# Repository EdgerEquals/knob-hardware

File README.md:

# knob-hardware

This repo holds the hardware for Ed's motorised knob and its Eurorack module (10HP).

- `cad/` is the parametric parts library. Each part folder has a build123d script, STEP, DXF and drawing PNG. The parts index is in `cad/README.md`.
- PCBs live in KiCad projects under `cad/pcbs/`, which are the single source of truth. Board STEPs are exported from KiCad and feed the mechanical assemblies.
- Dimensions marked [A] are assumed and need checking with calipers.
- `cad/knob-param/` (branch `param-dev`) is the sub-assembly-split parametric model of the whole knob stack, set up for parallel cloud-agent work. Start with `cad/knob-param/AGENTS.md`.

## Docs

- [Design notes](docs/design-notes.md): the current knob-module design (CAD v0.16), check status and open items.
- [Top screen joystick](docs/top-screen-joystick.md): the sliding screen carrier on the Alps SKRHADE010 and the switch shortlist.
- [Manufacturing (PCBWay)](docs/manufacturing-pcbway.md): the kit plan, what PCBWay builds, the cost target and reviewer questions.

The software engine lives in EdgerEquals/dad-page.

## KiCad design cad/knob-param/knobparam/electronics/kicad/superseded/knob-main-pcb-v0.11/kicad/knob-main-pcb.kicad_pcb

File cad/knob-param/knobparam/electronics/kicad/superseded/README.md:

# Superseded boards and tools (archived 10 Nov 2026)

Kept for the record only. **Nothing here is current, nothing here should be quoted or ordered**, and the scripts are not
run by the model (their relative paths broke when they moved here). See `docs/leftover-sweep-2026-11-10.md`.

| Folder | What it was | Replaced by |
|---|---|---|
| `knob-main-pcb-v0.11/` | main board v0.11 (generator, KiCad files, fab pack, STEP, DXF, drawing) | `../knob-main-pcb/v2/` (6 layers, routed, fab pack v2.0) |
| `screen-adapter-v0.4/` | screen adapter v0.4 (Ø15.5, CH32V003, FPC14) | the Ø12 rod-link board (v0.24) |
| `joystick-daughterboard-v0.4/` | joystick daughterboard v0.1/v0.4 (four M2 standoffs, 1x3 long headers) | the joystick top board on the vertical boards (layout v4); its `geom.json` stays in `../joystick-daughterboard/` because the model reads it |
| `v016-pipeline/` | the v0.16b board pipeline: `export_cad_constraints.py` → `cad_constraints.json` → `make_v016_footprints.py`, the old `export_pcb_proxy.py` (it wrote the same `pcb_proxy.json` the model reads, from the v0.11 board), `joystick_stack_v016.json` | `../knob-main-pcb/v2/design.py`, `make_board.py`, `export_proxy.py` |

`cad/pcbs/` (outside the model) is the separate v0.11 snapshot kept for `main`, untouched.

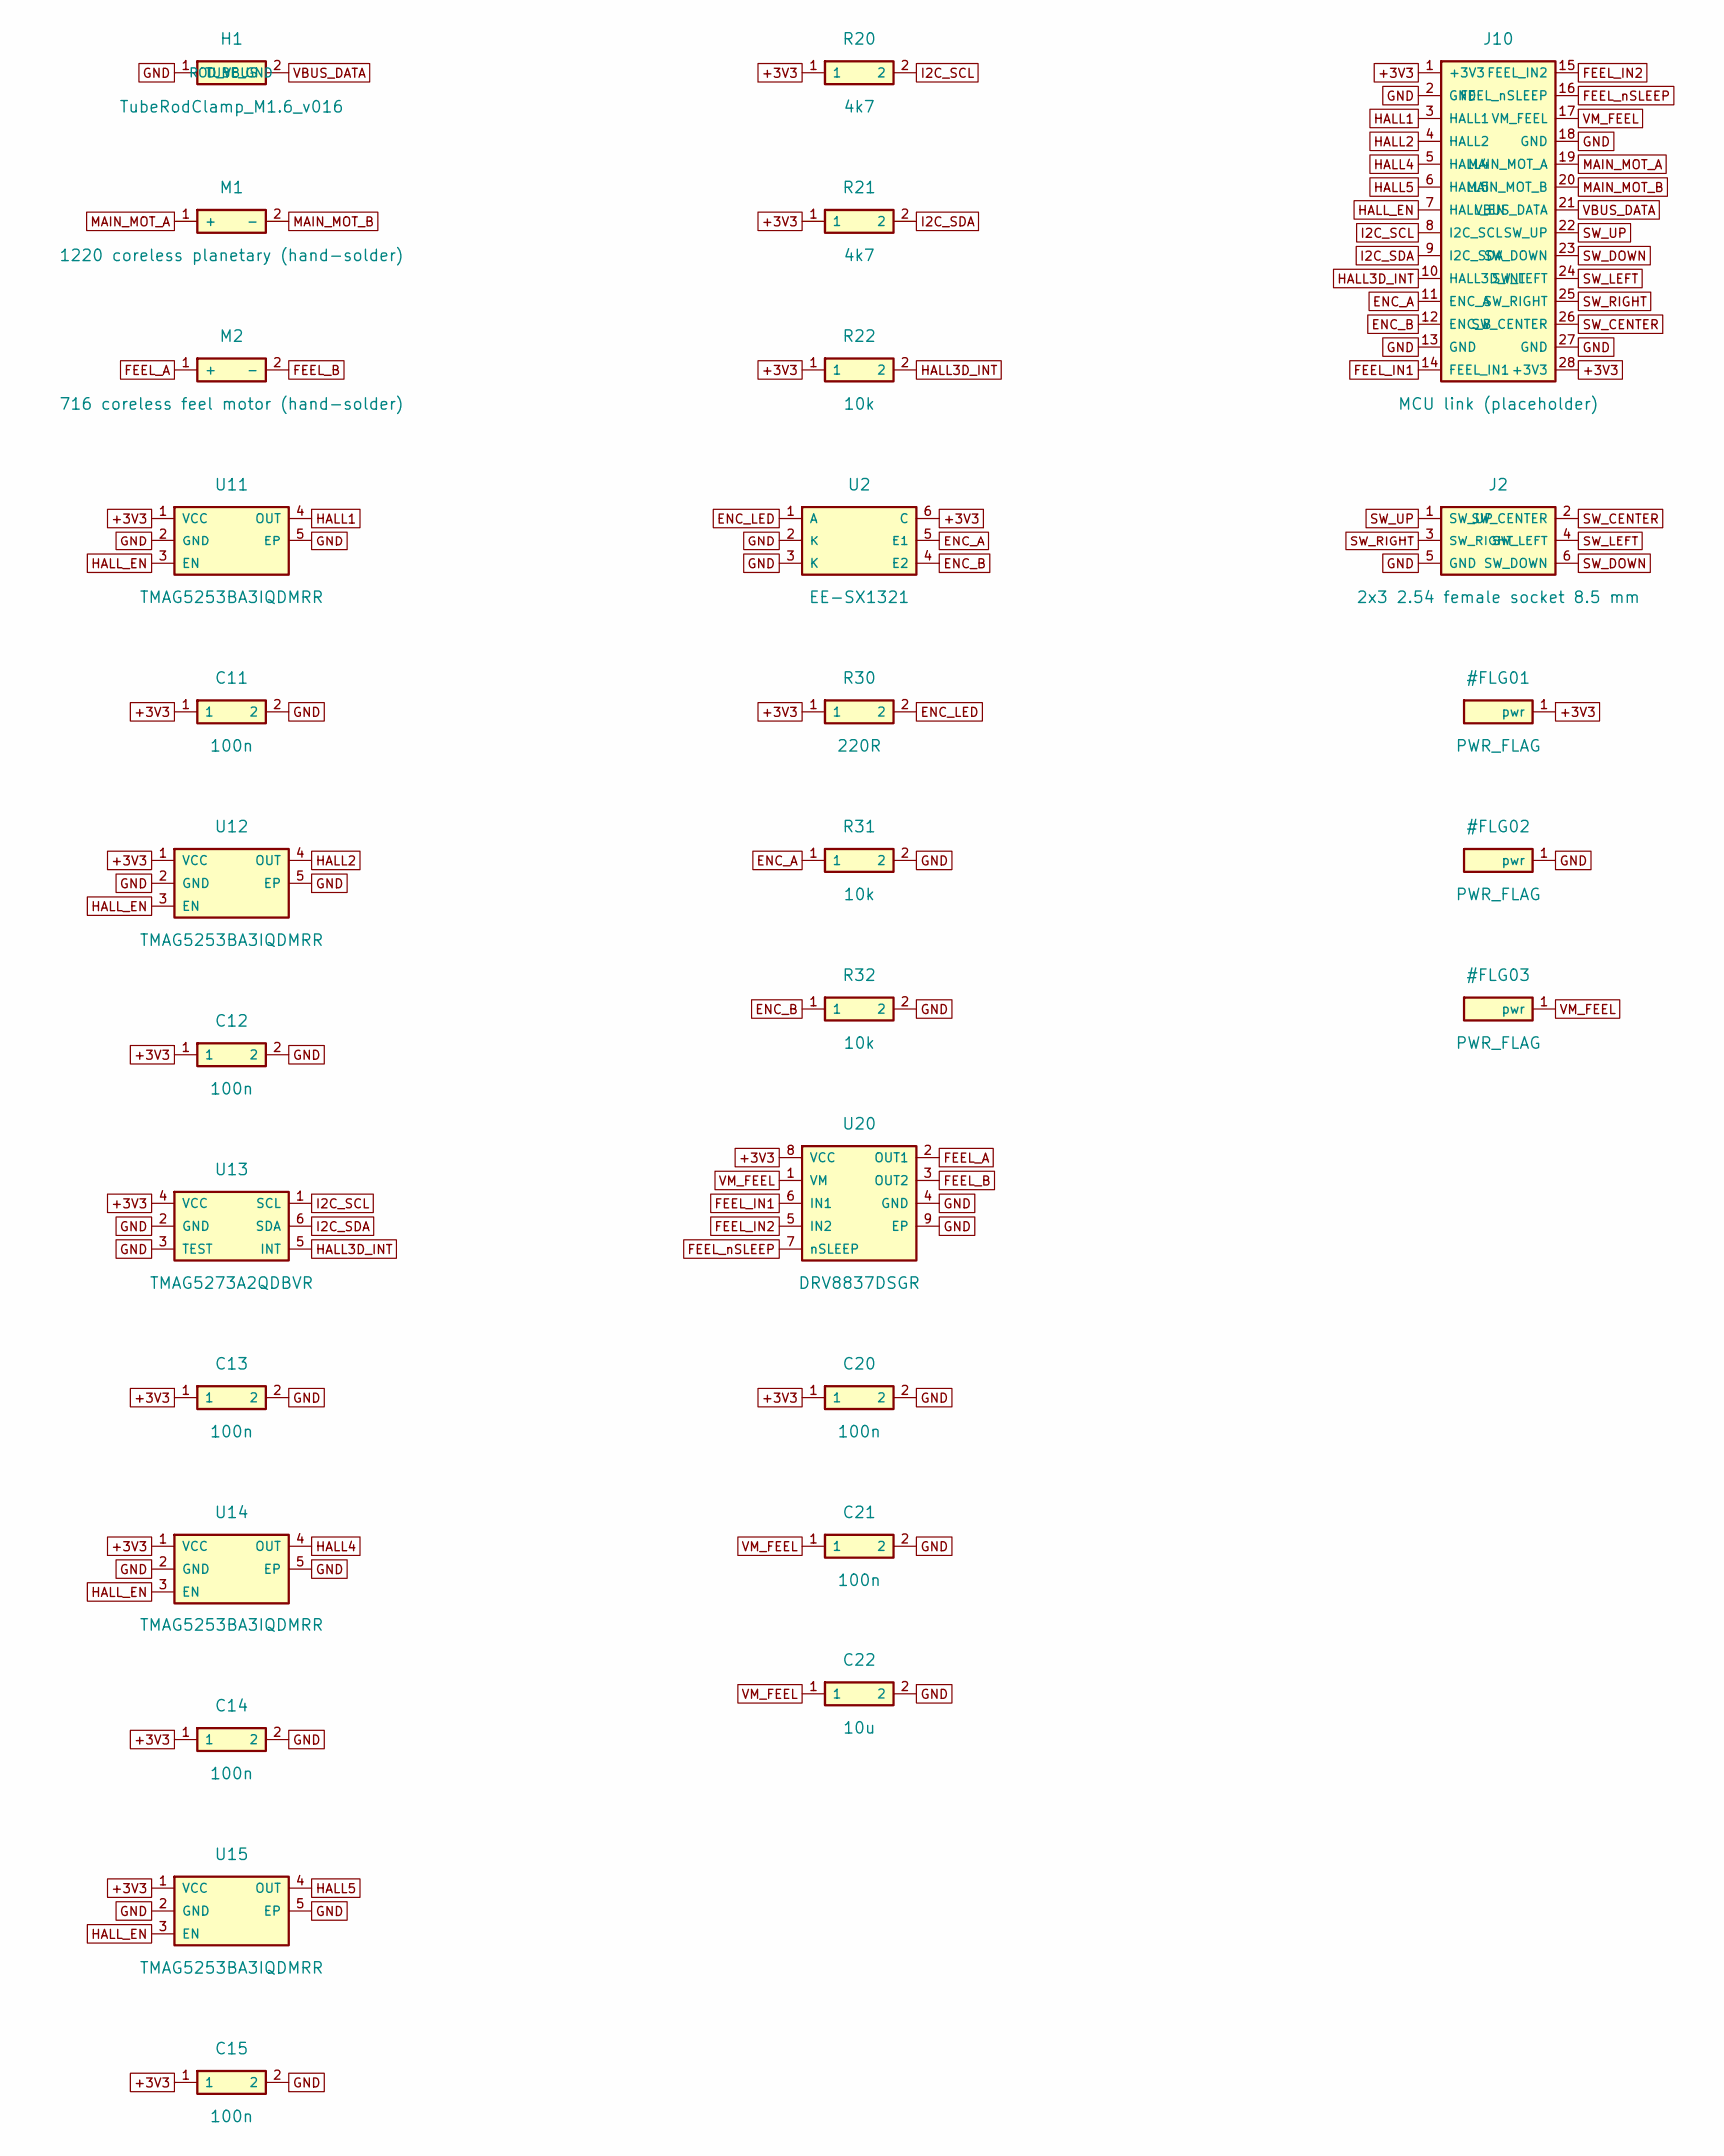
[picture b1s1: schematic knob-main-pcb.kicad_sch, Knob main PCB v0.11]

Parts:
C11, C12, C13, C14, C15, C20, C21: 100n; C_0402; MPN CL05B104KO5NNNC; LCSC C1525
C22: 10u; C_0603; MPN CL10A106KP8NNNC; LCSC C19702
H1: TubeRodClamp_M1.6_v016; TubeRodClamp_Main_M1.6_v016
J2: 2x3 2.54 female socket 8.5 mm; PinSocket_2x03_P2.54_Vertical_8.5mm; MPN FG-PM2.54-2-03P-H8.5; LCSC C42391433
J10: MCU link (placeholder); Pads_2x14_P2.00_SMD
M1: 1220 coreless planetary (hand-solder); Motor_1220_Tabs_Relief
M2: 716 coreless feel motor (hand-solder); FeelMotor_716_LeadPads
R20, R21: 4k7; R_0402; MPN 0402WGF4701TCE; LCSC C25900
R22, R31, R32: 10k; R_0402; MPN RC0402FR-0710KL; LCSC C60490
R30: 220R; R_0402; MPN 0402WGF2200TCE; LCSC C25091
U2: EE-SX1321; Omron_EE-SX1321; MPN EE-SX1321; LCSC C469128
U11, U12, U14, U15: TMAG5253BA3IQDMRR; X2SON-4_TMAG5253; MPN TMAG5253BA3IQDMRR; LCSC C22401868
U13: TMAG5273A2QDBVR; SOT-23-6_TMAG5273_Tight; MPN TMAG5273A2QDBVR; LCSC C3715882
U20: DRV8837DSGR; WSON-8_2x2_DRV8837; MPN DRV8837DSGR; LCSC C39159

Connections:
+3V3: C11.1, C12.1, C13.1, C14.1, C15.1, C20.1, J10.1 (+3V3), J10.28 (+3V3), R20.1, R21.1, R22.1, R30.1, U2.6 (C), U11.1 (VCC), U12.1 (VCC), U13.4 (VCC), U14.1 (VCC), U15.1 (VCC), U20.8 (VCC)
ENC_A: J10.11 (ENC_A), R31.1, U2.5 (E1)
ENC_B: J10.12 (ENC_B), R32.1, U2.4 (E2)
ENC_LED: R30.2, U2.1 (A)
FEEL_A: M2.1 (+), U20.2 (OUT1)
FEEL_B: M2.2 (-), U20.3 (OUT2)
FEEL_IN1: J10.14 (FEEL_IN1), U20.6 (IN1)
FEEL_IN2: J10.15 (FEEL_IN2), U20.5 (IN2)
FEEL_nSLEEP: J10.16 (FEEL_nSLEEP), U20.7 (nSLEEP)
GND: C11.2, C12.2, C13.2, C14.2, C15.2, C20.2, C21.2, C22.2, H1.1 (TUBE_GND), J2.5 (GND), J10.2 (GND), J10.13 (GND), J10.18 (GND), J10.27 (GND), R31.2, R32.2, U2.2 (K), U2.3 (K), U11.2 (GND), U11.5 (EP), U12.2 (GND), U12.5 (EP), U13.2 (GND), U13.3 (TEST), U14.2 (GND), U14.5 (EP), U15.2 (GND), U15.5 (EP), U20.4 (GND), U20.9 (EP)
HALL1: J10.3 (HALL1), U11.4 (OUT)
HALL2: J10.4 (HALL2), U12.4 (OUT)
HALL3D_INT: J10.10 (HALL3D_INT), R22.2, U13.5 (INT)
HALL4: J10.5 (HALL4), U14.4 (OUT)
HALL5: J10.6 (HALL5), U15.4 (OUT)
HALL_EN: J10.7 (HALL_EN), U11.3 (EN), U12.3 (EN), U14.3 (EN), U15.3 (EN)
I2C_SCL: J10.8 (I2C_SCL), R20.2, U13.1 (SCL)
I2C_SDA: J10.9 (I2C_SDA), R21.2, U13.6 (SDA)
MAIN_MOT_A: J10.19 (MAIN_MOT_A), M1.1 (+)
MAIN_MOT_B: J10.20 (MAIN_MOT_B), M1.2 (-)
SW_CENTER: J2.2 (SW_CENTER), J10.26 (SW_CENTER)
SW_DOWN: J2.6 (SW_DOWN), J10.23 (SW_DOWN)
SW_LEFT: J2.4 (SW_LEFT), J10.24 (SW_LEFT)
SW_RIGHT: J2.3 (SW_RIGHT), J10.25 (SW_RIGHT)
SW_UP: J2.1 (SW_UP), J10.22 (SW_UP)
VBUS_DATA: H1.2 (ROD_VBUS), J10.21 (VBUS_DATA)
VM_FEEL: C21.1, C22.1, J10.17 (VM_FEEL), U20.1 (VM)

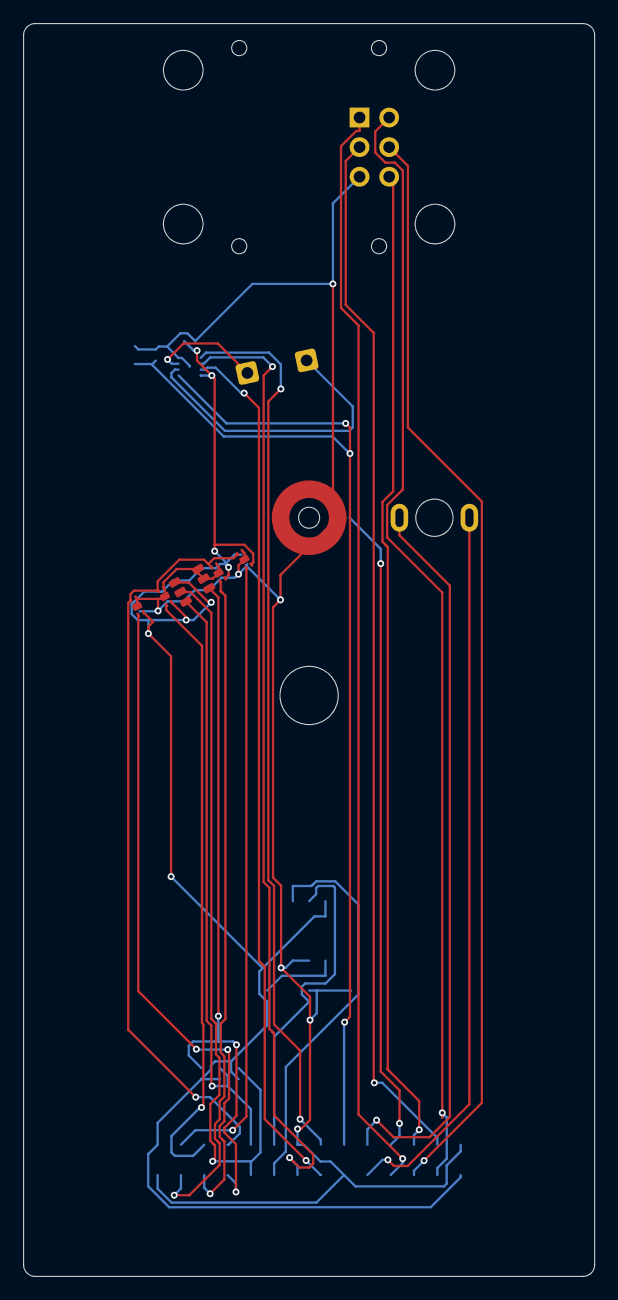
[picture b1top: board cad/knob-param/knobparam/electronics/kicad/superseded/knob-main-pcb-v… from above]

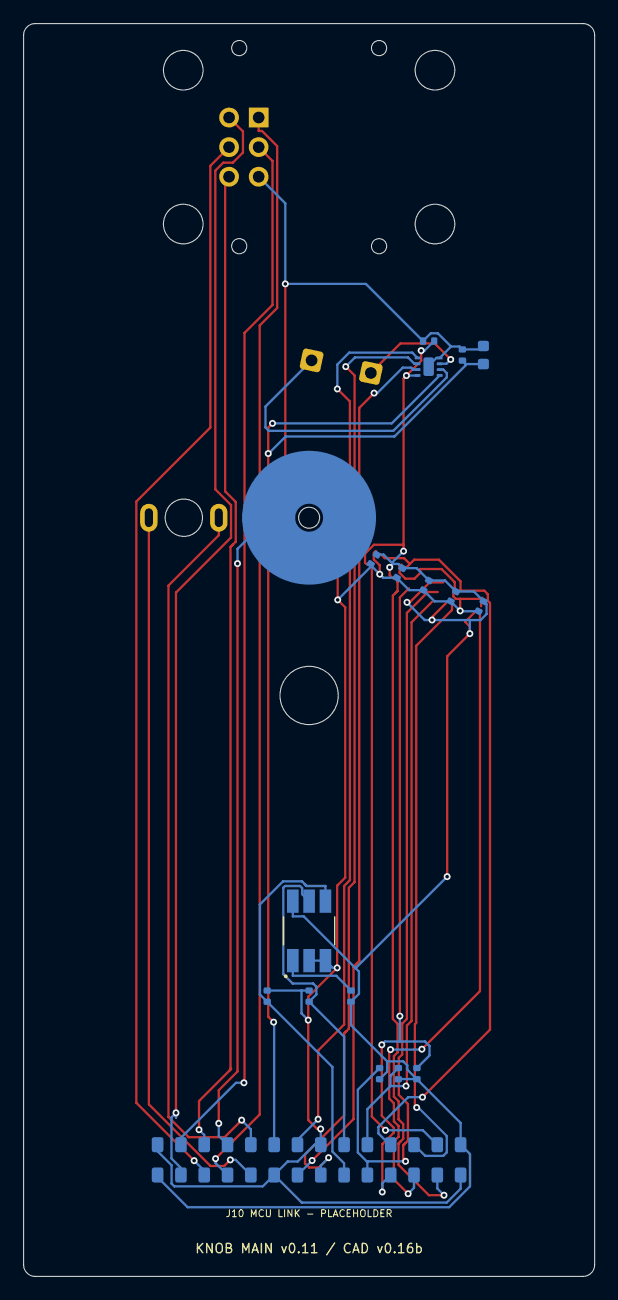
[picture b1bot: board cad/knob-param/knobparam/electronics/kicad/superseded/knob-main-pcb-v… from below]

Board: 2 copper layers, 49.0 x 107.5 mm, 28 parts (18 on the bottom side), 27 nets.

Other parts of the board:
H2: Bearing_F682ZZ_Press_NPTH_5.0mm
MH1: TopScreenJoystick_Stack_v016

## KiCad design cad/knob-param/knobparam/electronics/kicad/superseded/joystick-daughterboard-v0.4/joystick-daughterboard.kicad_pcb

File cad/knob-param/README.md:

# knob-param

Parametric CAD (build123d) for the motorised Eurorack knob, split into five sub-assemblies plus an
assembly layer that owns the interface params, cross-checks and render. Default = v0.15.

```bash
bash setup.sh && .venv/bin/python build.py --render     # -> ../assemblies/knob-stack-v0.15/
```

Workflow, contract and commands: [AGENTS.md](AGENTS.md).

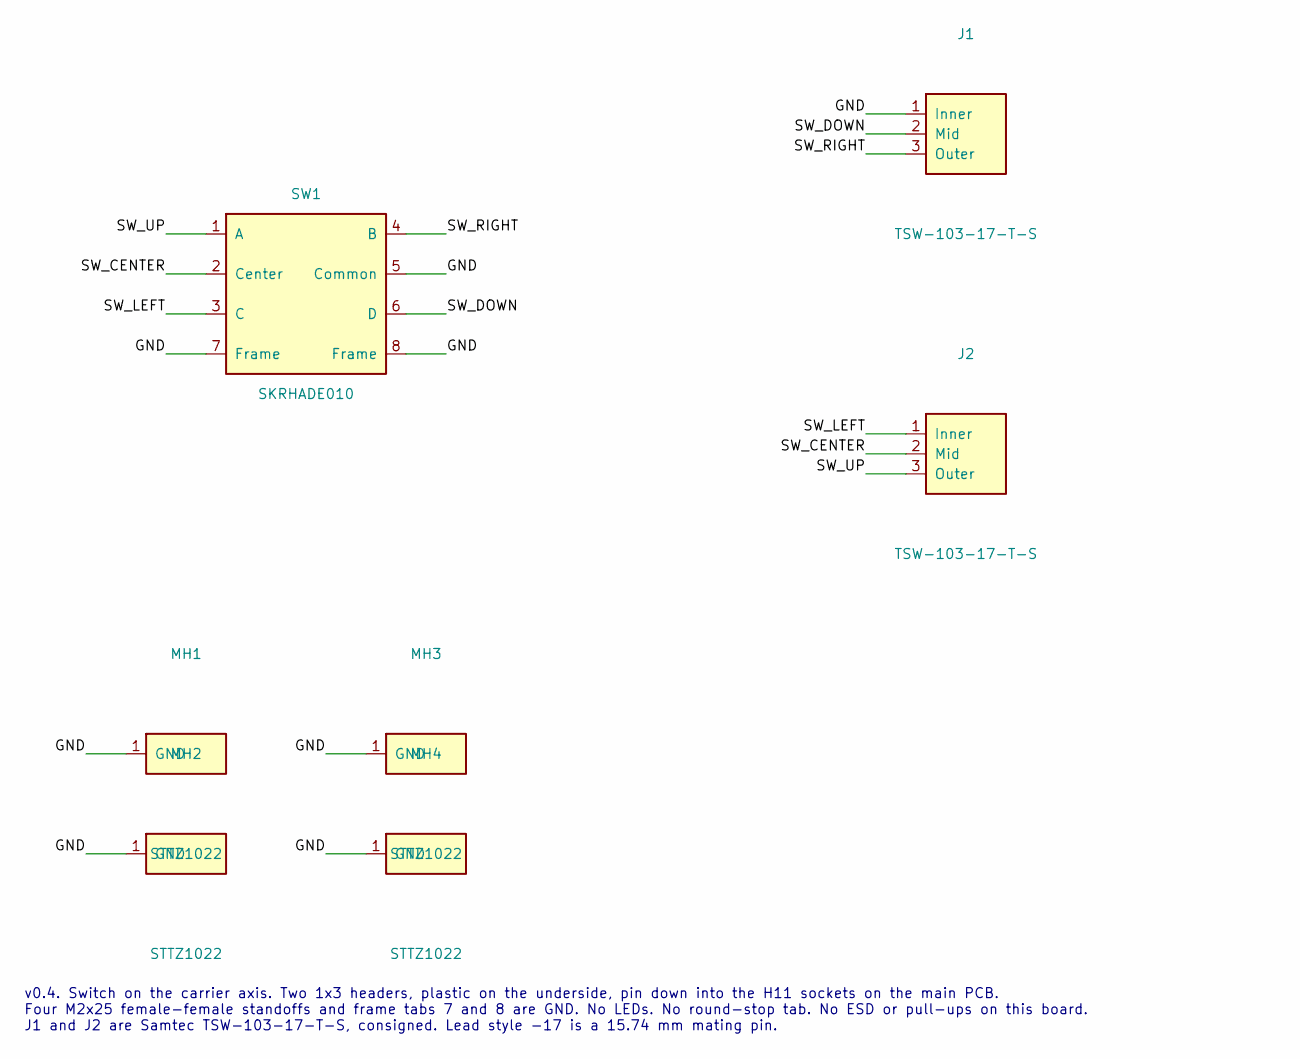
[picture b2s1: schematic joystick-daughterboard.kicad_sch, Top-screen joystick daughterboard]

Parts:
J1, J2: TSW-103-17-T-S; PinHeader_1x03_P2.54mm_Vertical_Long; MPN TSW-103-17-T-S
MH1, MH2, MH3, MH4: STTZ1022; Mount_M2x35_Standoff; MPN STTZ1022; LCSC C50378470
SW1: SKRHADE010; Alps_SKRHADE010; MPN SKRHADE010; LCSC C202415

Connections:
/GND: J1.1 (Inner), MH1.1, MH2.1, MH3.1, MH4.1, SW1.5 (Common), SW1.7 (Frame), SW1.8 (Frame)
/SW_CENTER: J2.2 (Mid), SW1.2 (Center)
/SW_DOWN: J1.2 (Mid), SW1.6 (D)
/SW_LEFT: J2.1 (Inner), SW1.3 (C)
/SW_RIGHT: J1.3 (Outer), SW1.4 (B)
/SW_UP: J2.3 (Outer), SW1.1 (A)

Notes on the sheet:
v0.4. Switch on the carrier axis. Two 1x3 headers, plastic on the underside, pin down into the H11 sockets on the main PCB. Four M2x25 female-female standoffs and frame tabs 7 and 8 are GND. No LEDs. No round-stop tab. No ESD or pull-ups on this board. J1 and J2 are Samtec TSW-103-17-T-S, consigned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

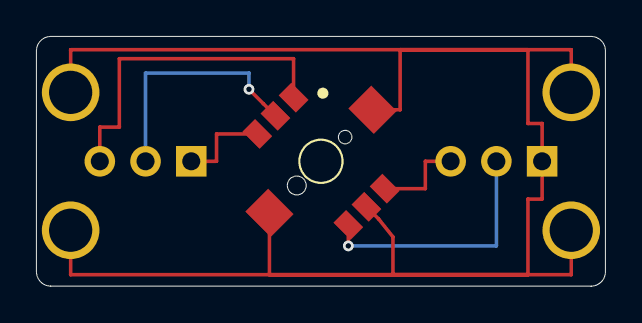
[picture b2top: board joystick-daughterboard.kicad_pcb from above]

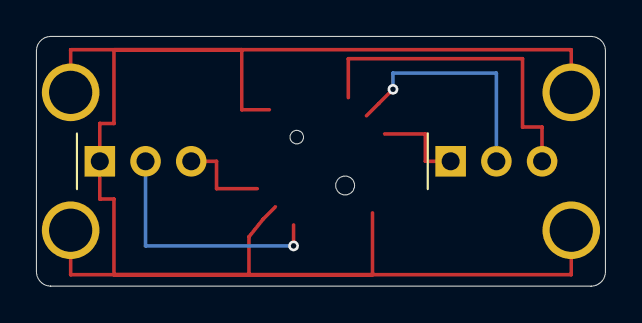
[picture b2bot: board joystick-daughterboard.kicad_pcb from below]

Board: 2 copper layers, 31.6 x 13.9 mm, 7 parts (2 on the bottom side), 6 nets.

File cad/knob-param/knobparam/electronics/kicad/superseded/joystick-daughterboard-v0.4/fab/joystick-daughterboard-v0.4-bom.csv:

Item,Designator,Qty,Value,Footprint,Manufacturer,MPN,LCSC
1,"J1,J2",2,TSW-103-17-T-S,PinHeader_1x03_P2.54mm_Vertical_Long,Samtec,TSW-103-17-T-S,
2,"MH1,MH2,MH3,MH4",4,STTZ1022,Mount_M2x35_Standoff,XHHD,STTZ1022,C50378470
3,SW1,1,SKRHADE010,Alps_SKRHADE010,Alps Alpine,SKRHADE010,C202415

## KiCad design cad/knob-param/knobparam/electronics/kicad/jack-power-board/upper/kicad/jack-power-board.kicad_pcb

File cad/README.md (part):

# Parts library

These are the parametric CAD parts for Ed's hardware. Each part has its own folder with the build123d script, a STEP file, a DXF and a drawing PNG.
Dimensions marked [A] are assumed and need checking with calipers. Status is either "listing" (dimensions from listings) or "measured".

| Part | Folder | Version | Status | Notes |
|---|---|---|---|---|
| 1220 coreless planetary gearmotor, 1:144 | motors/1220-coreless-planetary | v0.1 (2026-10-31) | listing | Chosen for knob v1. Ø12 × 38 mm, plus a 5.5 mm D-shaft. Mounting holes TBC. |
| N30 planetary gearmotor | motors/n30-planetary | v0.1 (2026-10-31) | listing | Made from motor_gearbox.py in the 1220 folder by swapping parameters. |
| Knob main PCB | pcbs/knob-main-pcb | v0.9 (2026-10-31) | layout v5 | **Source is KiCad** (kicad/knob-main-pcb.kicad_pcb, made by kicad/make_board.py, KiCad 9.0.2; DRC clean). Plain Edge.Cuts outline 49.00 × 107.50 × 1.6, at x 0.75–49.75, y 10.5–118.0 from the panel top-left. H1 = footprints:Shaft_Hole_NPTH_5.2mm on the dial axis (v0.3: was 6.2; sized for the Ø5.0 brass tube + 0.1 per side [A]). v0.5: H2 is flipped to the back (B side), so the F682ZZ presses in from the PCB back with its flange on the back face; DRC clean, STEP re-exported. v0.4 added H2 = footprints:Bearing_F682ZZ_Press_NPTH_5.0mm (Ø5.0 NPTH press fit for the encoder bearing [A]) at (25.25, 71.9), 19.0 below the dial axis (25.25, 52.9). M1 = footprints:Motor_1220_Tabs at the motor position (39.25, 52.9): 14.0 mm right of the dial axis [A, motor offset TBC, gear/belt drive TBC]. The STEP comes from kicad-cli; knob_main_pcb.py only reads and draws it. | **v0.6:** H2 back on the FRONT (no flip): encoder bearing 1 goes in from the front through the base cradle floor into H2 (locating dowel); hole Ø5.0 NPTH unchanged; DRC 0; STEP re-exported. **v0.7:** H2 rotated 3.0° [A] about the dial axis (idler pinion clearance to the motor). **v0.8:** H1 = TubeRodClamp_Main_M1.6: NPTH Ø1.8 for the M1.6 rod, F.Cu ring Ø3.4–Ø6.4 net GND (brass tube soldered), B.Cu ring Ø2.4–Ø4.4 net VBUS_DATA (rod washer/nut). DRC 0, STEP re-exported. **v0.9:** motor M1 offset 14.0 → 11.0 (32T hub gear), H2 16.0 below the axis on the centre line (ENC_SET_ROT 0), U2 Omron_EE-SX1131 on B.Cu 20.20 below H2; DRC 0, STEP re-exported; sheet v0.9. |
| Knob stack (PCB + 1220 motor) | assemblies/knob-stack-v0.1 | v0.1 (2026-10-31) | superseded by v0.2 | Snapshot: motor on the dial axis, no shaft. The files are kept as drawn; if re-run, the script would pick up the v0.2 board. |
| Knob stack v0.2 (PCB + offset 1220 motor + 6 mm shaft) | assemblies/knob-stack-v0.2 | v0.2 (2026-10-31) | SUPERSEDED by v0.3 | knob_stack.py places everything from the KiCad positions. The shaft base flange sits on the PCB back and the shaft passes through H1; it stands 43.5 above the PCB front (45.0 − the 1.51 STEP board). The motor is on the front at M1: 38.0 mm body, 43.5 mm to its shaft tip. **Clash: the 49 × 49 flange covers the motor tab slots, and the tabs reach about 1 mm into the flange. Flange needs relief for motor tabs [check].** |
| Knob stack v0.3 (PCB + offset 1220 motor + brass 5×3 shaft) | assemblies/knob-stack-v0.3 | v0.3 (2026-10-31) | SUPERSEDED by v0.4 | Contains only the PCB, the 1220 motor at its 14.0 [A] offset (M1), and the brass tube with the printed 17.5 × 17.5 × 4.0 flange. The flange is bonded to the PCB back face. The tube passes through H1 (Ø5.2 NPTH) and runs forward, its back end flush with the flange back. Tube top is 43.49 above the PCB front (45.0 − the 1.51 STEP board). Motor is 38.0, 43.5 to its shaft tip. Flange to the nearest tab pad: 1.50. Pairwise clash check (tube/PCB, tube/motor, flange/PCB, flange/motor): none. Files: knob_stack.py, knob-stack-v0.3.{step,dxf}, knob-stack-v0.3-drawing.png |
| Knob stack v0.4 (all current parts) | assemblies/knob-stack-v0.4 | v0.4 (2026-10-31) | SUPERSEDED by v0.5 | Every part is imported from the library, with no new geometry. Parts: PCB v0.3 (KiCad STEP); 1220 motor at the 14.0 [A] offset; brass shaft v0.2 (57.31 tube plus the 17.5 × 4.0 flange); knob v0.1 (cap + hub, internal ring, bottom ring, pinion, bronze bush); screen holder v0.1; 0.71" GC9D01 TFT; screen adapter board. Key dimensions: 57.00 overall above the PCB front (glass top), knob OD 38.25 (gear tip Ø40.5), holder OD 22.32, motor offset 14.0. Pairwise interference: 16 parts, 120 pairs, 27 with overlapping bounding boxes checked. **Clashes (red on the sheet):** PCB/motor 4.24 mm³ (the motor rear boss Ø3 × 0.6 [A] goes into the PCB front); holder vs. TFT backing 10.20, glass 13.76 and tail 7.43 mm³ (COG ledge and folded tail go through the holder wall). **Notes:** knob OD ≥ the Ø35 bezel; the supplied 100 mm tail needs a short-tail variant. Files: knob_stack.py, knob-stack-v0.4.{step,dxf}, knob-stack-v0.4-drawing.png |
| Knob stack v0.5 (all current parts) | assemblies/knob-stack-v0.5 | v0.5 rev B (2026-10-31) | superseded by v0.6 | **Rev B:** the front view is now full section A-A, cut on the plane through the dial and motor axes (world XZ at the dial y), drawn front-up like the plan. Every cut part has its own hatch: PCB, motor, brass tube, flange, cap+skirt, 68T ring, 90T bottom ring, pinion, bush, encoder big gear (chord), holder, TFT backing, TFT glass, adapter board. The encoder pinion, shaft and bearings are off the plane. The cutting line A-A with arrows is on the side view, because the plane is parallel to the plan view. Same parts as v0.4, but with knob v0.2 (skirt round the motor, 90T bottom internal ring), PCB v0.4 (H2) and encoder take-off v0.1; all imported from the library. The back panel is a dashed line only, 25 [A] behind the PCB back. 57.00 overall above the PCB front; skirt OD 48.00 (ring band Ø49.25); holder OD 22.32; motor offset 14.0; skirt 2.0 above the PCB. Pairwise check: 21 parts, 210 pairs, 33 with overlapping bounding boxes. **Clashes (red):** PCB/motor 4.24 mm³ (motor rear boss Ø3 × 0.6 [A]); holder vs. TFT backing 10.20, glass 13.76 and tail 7.43 mm³. The skirt and the encoder parts clash with nothing. **Notes (red):** the skirt OD is over the 49 PCB width and the Ø35 bezel; the big gear is behind the PCB [A], passing under the shaft flange and the tube's wire exit; the 100 mm tail needs a short-tail variant. Files: knob_stack.py, knob-stack-v0.5.{step,dxf}, knob-stack-v0.5-drawing.png |
| Knob stack v0.6 (all current parts) | assemblies/knob-stack-v0.6 | v0.6 rev A (2026-10-31) | superseded by v0.7 | v0.5 plus bezel v0.1, with knob v0.3 (PTFE 10x8 liner instead of the bronze bush), encoder take-off v0.2 (bearing 1 from the PCB back) and PCB v0.5. Front view = full section A-A through the dial and motor axes, each cut part hatched differently (bezel and PTFE liner now in the cut); the A-A line is on the side view. The screen holder (unchanged) now sits on the bezel face at 47.30, 1.50 higher, so the holder, screen and adapter move up 1.50; overall 58.50 above the PCB front. 22 parts, 231 pairs, 42 with overlapping bounding boxes. **Clashes (red):** PCB/motor 4.24 mm³ (motor rear boss); holder vs. TFT backing 10.20, glass 13.76, tail 7.43 mm³. Bezel, liner and encoder parts clash with nothing. **Notes (red):** tube v0.2 now engages the holder socket only 4.50 of 6.0 (tube +1.50 = 58.81 if wanted; not changed); skirt OD over the board and bezel; big gear behind the PCB; 100 mm tail. Also a shaded isometric half-section (iso_section.py → knob-stack-v0.6-iso-section.png, knob-stack-v0.6-half-section.step; pyvista offscreen, near half removed, cut faces lighter, clashes red). Files: knob_stack.py, iso_section.py, knob-stack-v0.6.{step,dxf}, knob-stack-v0.6-drawing.png |
| Knob stack v0.7 (all current parts) | assemblies/knob-stack-v0.7 | v0.7 rev B (2026-10-31) | superseded by v0.8 | **Rev B (Ed: top-left must be a top view; the right view rotated 90°):** sheet in the new z-up layout. Top-left = TOP view looking down the dial axis (board outline, knob, gears, A-A cutting line with arrows); bottom-left = FRONT = section A-A (Z up, board at the bottom, shaft up); right = RIGHT SIDE view with Z up, so the PCB faces, knob top and shaft tip line up with the section. Notes moved beside the top view. v0.6 with bezel v0.1 → bezel knob v0.2 (Ø48 ring on the big knob, top flush with the glass, ±10° [A]); holder/screen/adapter 1.80 above the holder v0.1 frame (base 47.60). Overall 58.80 above the PCB front. Sheet: section A-A front view, plan and side views. 22 parts, 231 pairs, 50 bbox-overlapping. **Clashes (red):** PCB/motor 4.24 mm³; bezel knob vs TFT backing 13.76, glass 16.53, tail 5.24 mm³ (COG ledge and folded tail into the pocket wall; new); holder vs TFT backing 10.20, glass 13.76, tail 7.43 mm³. **Notes (red):** tube engagement 4.20 of 6.0; skirt OD; big gear behind the PCB; 100 mm tail. Isometric half-section: knob-stack-v0.7-iso-section.png + knob-stack-v0.7-half-section.step (the screen clashes lie in the removed half and are shown whole). Files: knob_stack.py, iso_section.py, knob-stack-v0.7.{step,dxf}, knob-stack-v0.7-drawing.png |
| Knob stack v0.8 (all current parts) | assemblies/knob-stack-v0.8 | v0.8 rev A (2026-10-31) | superseded | knob_stack.py (z-up sheet, section A-A through dial + motor axes, 21 parts, pairwise clash check: PCB/motor 4.24 and the known TFT ledge/tail clashes vs holder and control dial; no tube, cradle or gear clash), iso_section.py (iso half-section PNG + STEP), export_mobile.py (GLB + USDZ full and half-section, m, Y up, coloured per part, re-import checked). Parts: PCB v0.6, base cradle v0.3, brass tube v0.2 (now 4.0 proud of the PCB back, flagged), control dial v0.3, big knob v0.4, encoder v0.3, screen holder v0.2, TFT, adapter. |
| Knob stack v0.9 (all current parts) | assemblies/knob-stack-v0.9 | v0.9 rev A (2026-10-31) | superseded by v0.10 | 32 parts; section A-A through the dial + motor axes, pairwise clash check, iso half-section, GLB + USDZ (whole + half). Big knob v0.5 + 688ZZ, control dial v0.4 + magnet placeholder, screen holder v0.4, brass tube v0.4 + M1.6 rod/sleeve/nuts, base cradle v0.4 (3.5 plate), encoder v0.4 + 2 idler pinions on Ø1.5 pins, PCB v0.8, adapter v0.2. Clashes left: PCB/motor rear boss 4.24 and the known TFT ledge/tail vs holder and control dial. |
| Knob stack v0.10 (all current parts) | assemblies/knob-stack-v0.10 | v0.10 rev A (2026-10-31) | superseded by v0.11 | v0.9 with big knob v0.6 (raised rim removed; top face 52.50, 4.30 below the glass; knob height 50.5) and control dial v0.5 (4.0 lip out to the full Ø48 on top of the knob, 0.3 [A] running gap; magnet placeholder Ø39.4×Ø43.4×2.0 [A] in a pocket in the lip underside, facing the knob top 0.3 below). Bearing 688ZZ → MR128ZZ 8×12×3.5 [A] (40.10–43.60) on the unchanged Ø8.12 dial tube; knob hub Ø19.0 → Ø15.0, outer race on a Ø10.6 bottom lip, dial bears on the inner race through a Ø9.2 collar. 32 parts; clashes unchanged from v0.9 (PCB/motor rear boss 4.24, TFT ledge/tail vs holder and control dial); no knob/dial/bearing clash. Files: knob_stack.py, iso_section.py, export_mobile.py, knob-stack-v0.10.{step,dxf,glb,usdz}, -half-section.{step,glb,usdz}, -drawing.png, -iso-section.png |
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
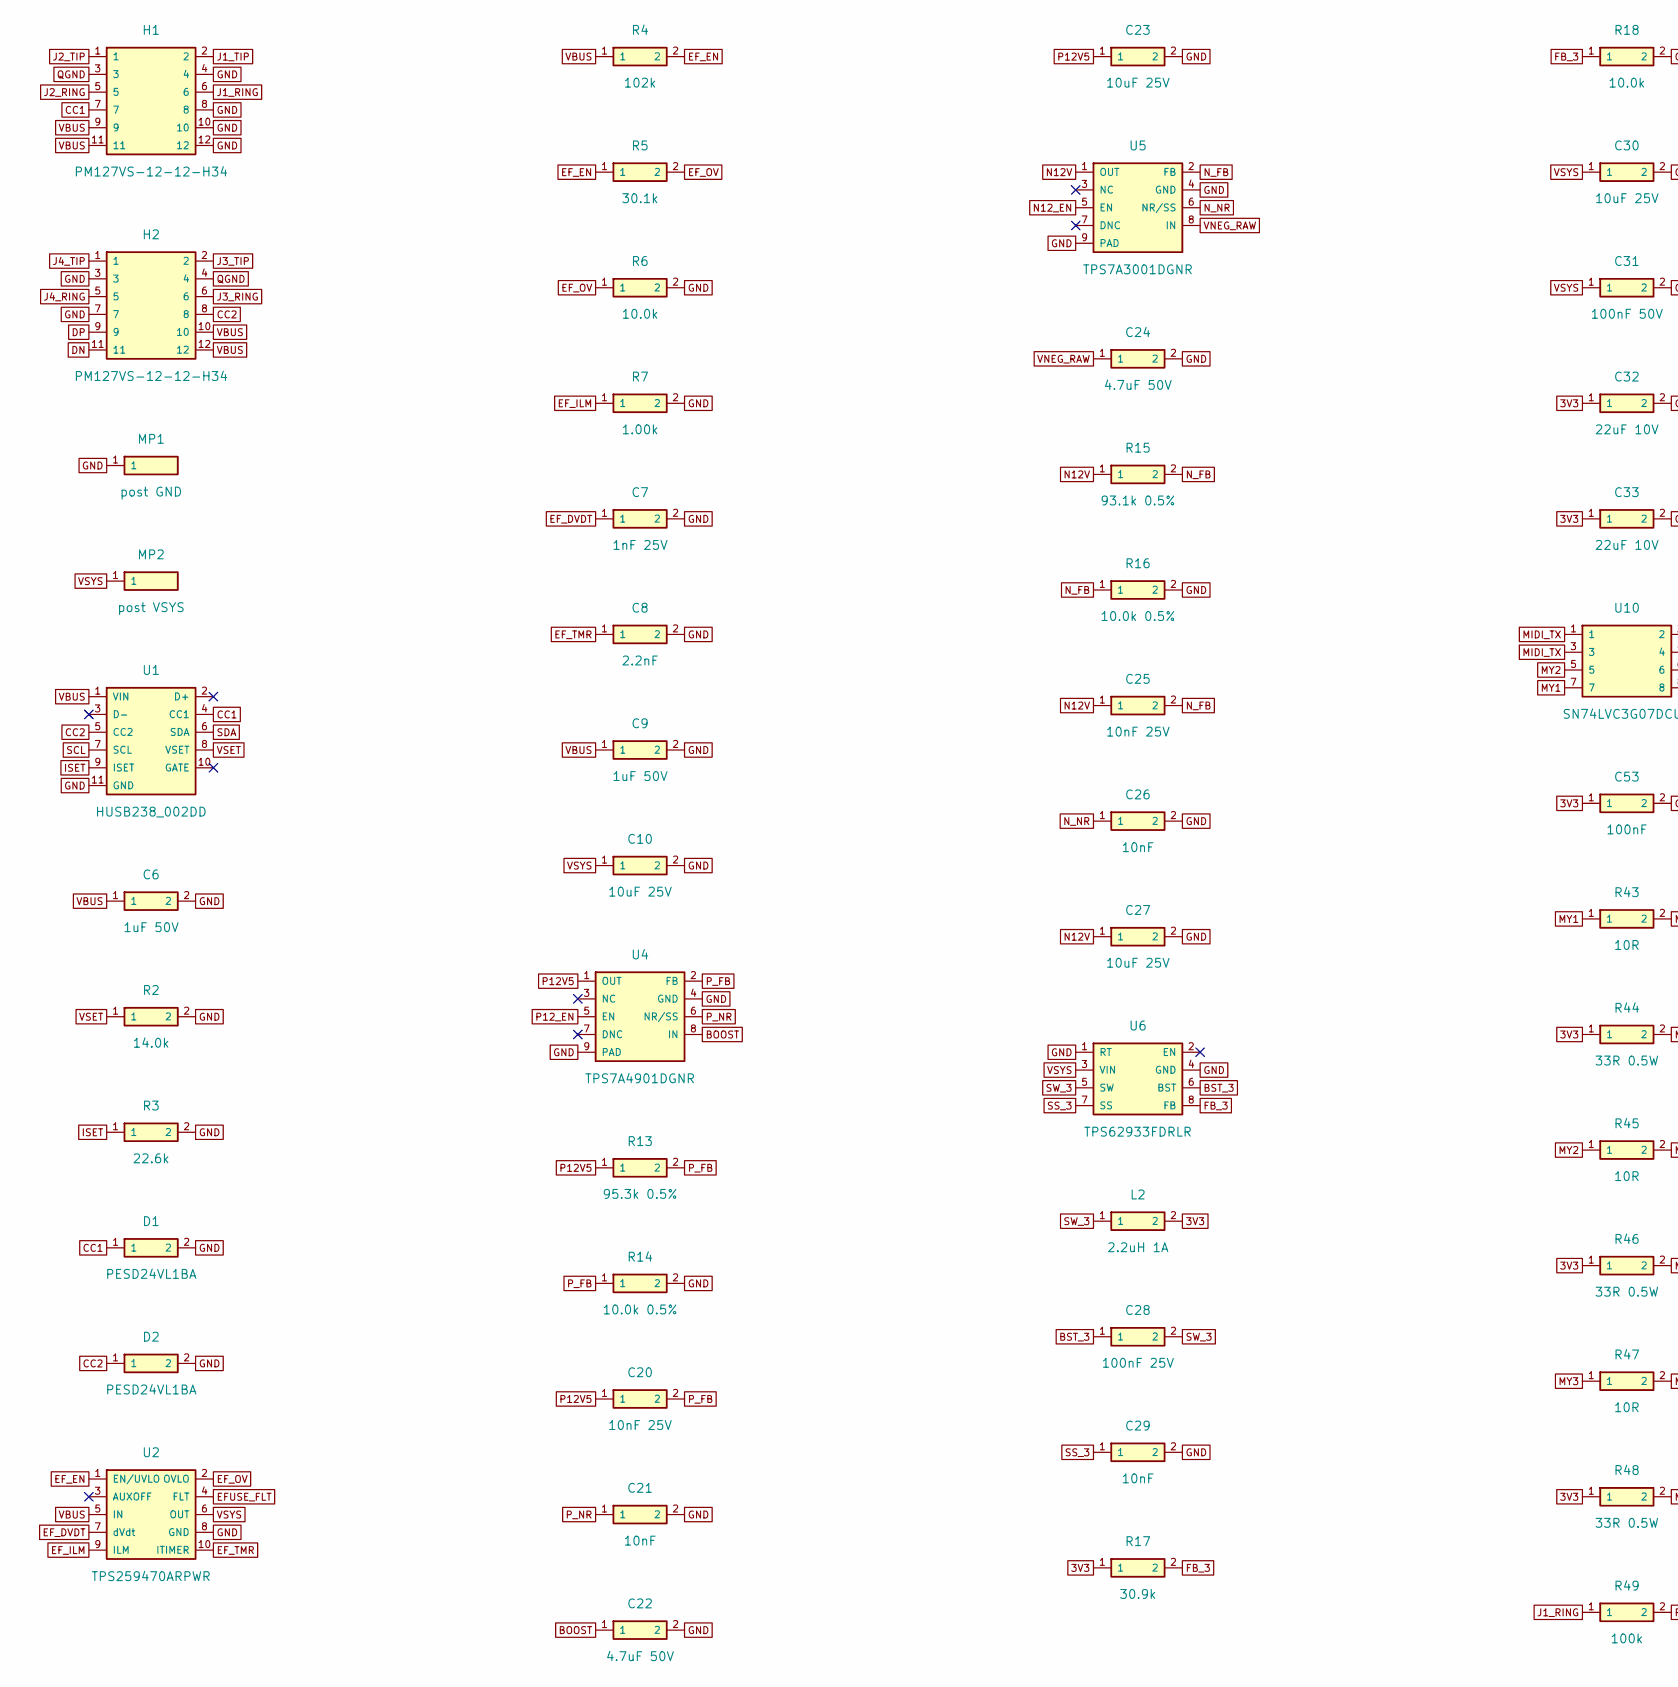
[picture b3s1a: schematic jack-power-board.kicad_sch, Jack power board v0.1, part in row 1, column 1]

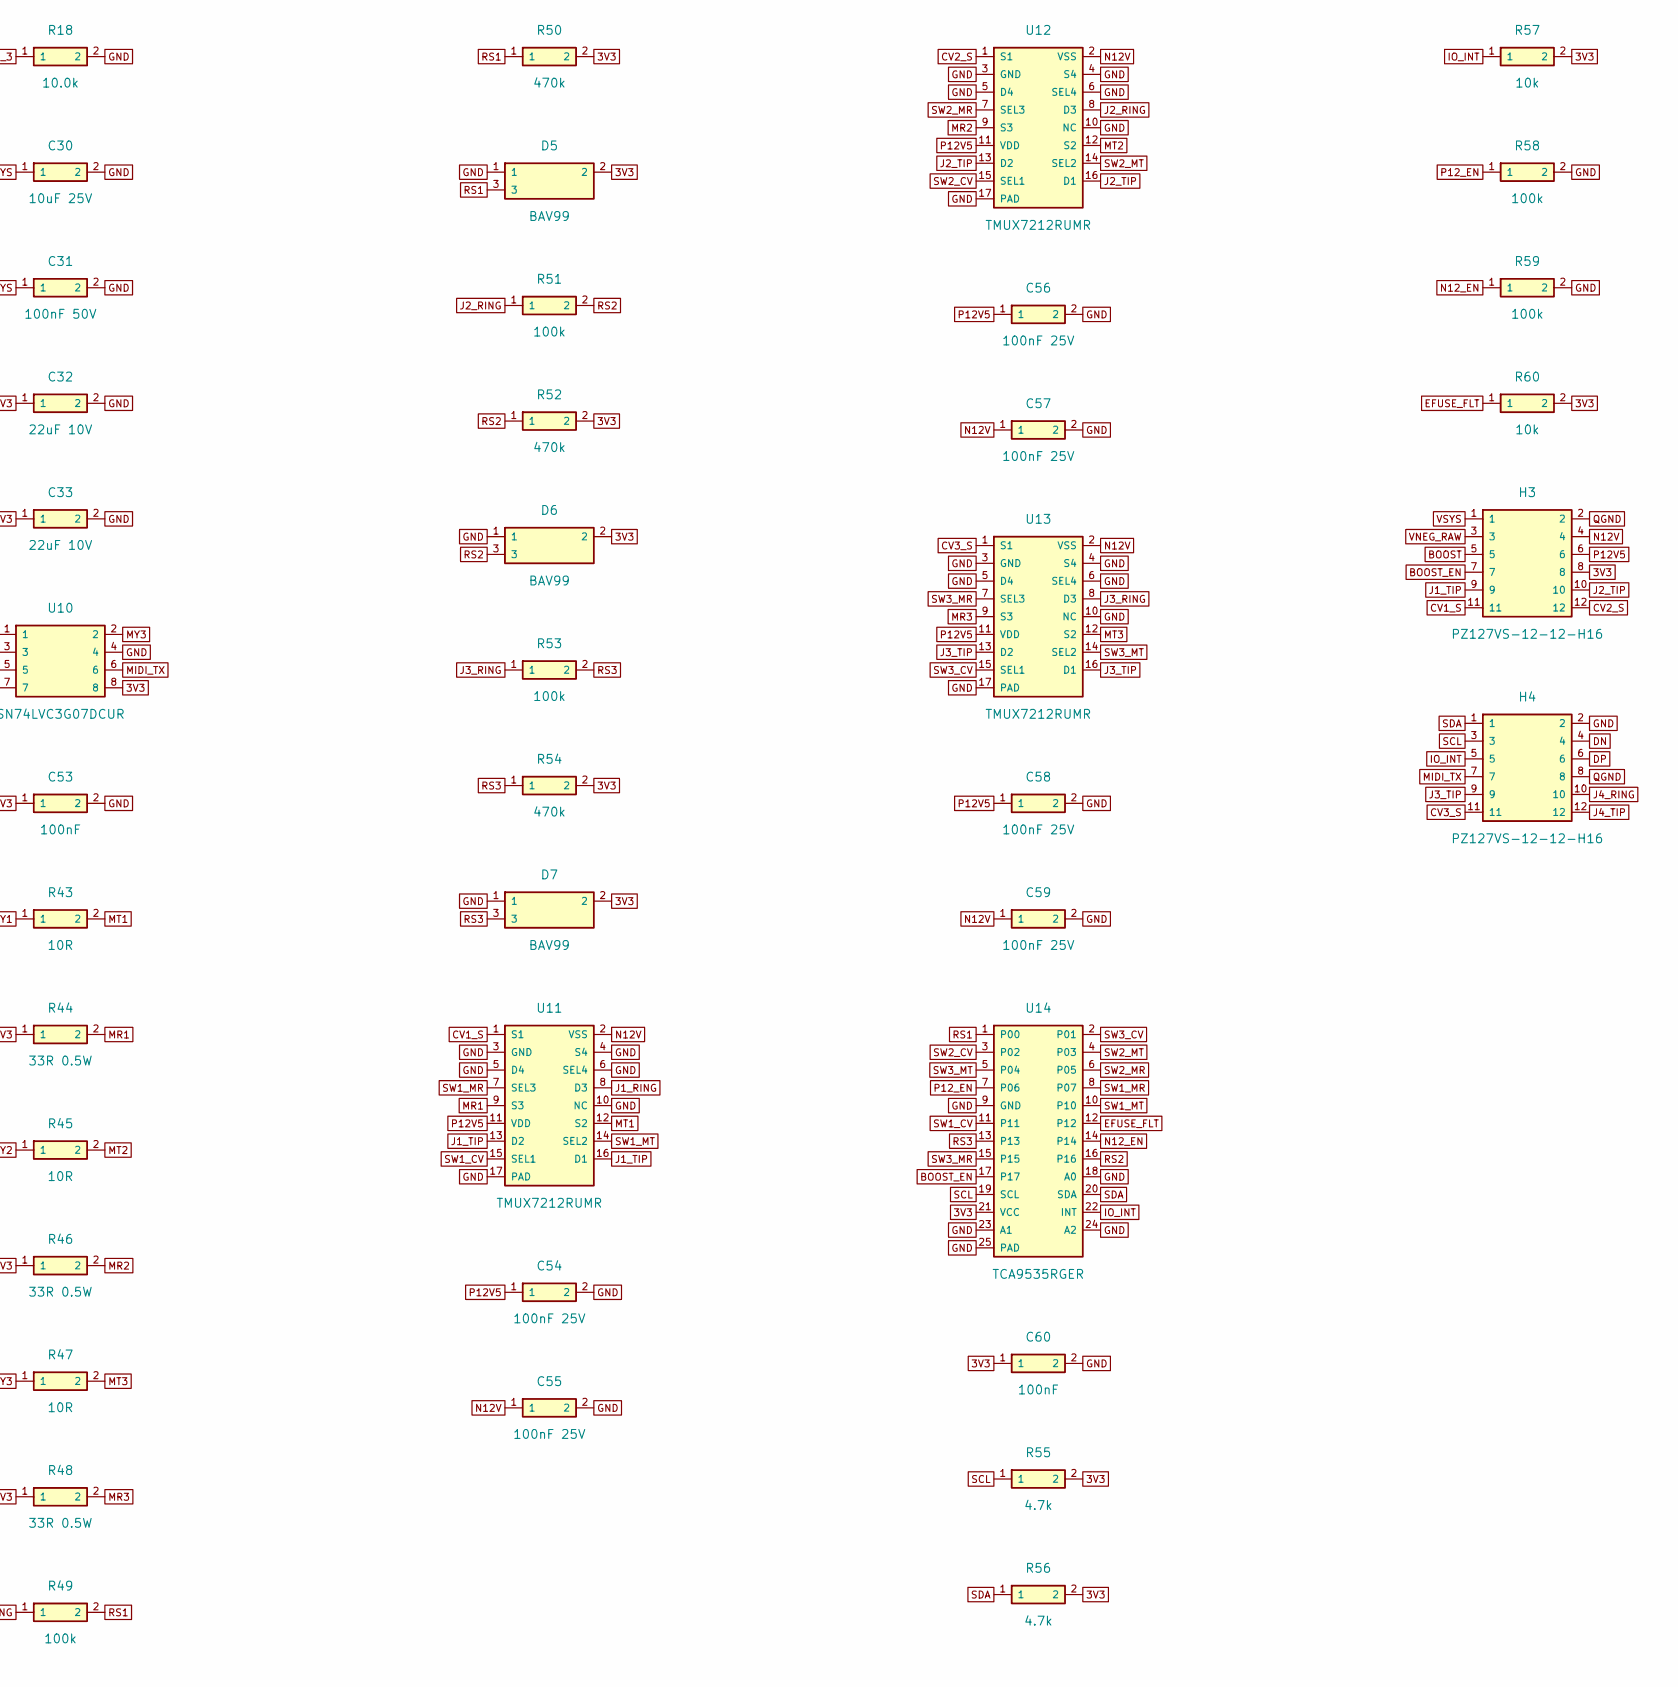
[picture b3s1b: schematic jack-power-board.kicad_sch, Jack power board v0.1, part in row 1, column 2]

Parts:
C6, C9: 1uF 50V; C_0603_1608Metric
C7: 1nF 25V; C_0402_1005Metric
C8: 2.2nF; C_0402_1005Metric
C10, C23, C27, C30: 10uF 25V; C_0805_2012Metric
C20, C25: 10nF 25V; C_0402_1005Metric
C21, C26, C29: 10nF; C_0402_1005Metric
C22, C24: 4.7uF 50V; C_0805_2012Metric
C28, C54, C55, C56, C57, C58, C59: 100nF 25V; C_0402_1005Metric
C31: 100nF 50V; C_0402_1005Metric
C32, C33: 22uF 10V; C_0805_2012Metric
C53, C60: 100nF; C_0402_1005Metric
D1, D2: PESD24VL1BA; D_SOD-323; MPN PESD24VL1BA,115; LCSC C69324
D5, D6, D7: BAV99; SOT-23; MPN BAV99; LCSC C2500
H1, H2: PM127VS-12-12-H34; PinSocket_2x06_P1.27mm_Vertical_SMD; MPN PM127VS-12-12-H34-4.5-R; LCSC C2840010
H3, H4: PZ127VS-12-12-H16; PinHeader_2x06_P1.27mm_Vertical_SMD; MPN PZ127VS-12-12-H16-4.5-R; LCSC C2840009
L2: 2.2uH 1A; L_Cenker_CKCS252012
MP1: post GND; Post_Pin_1.0
MP2: post VSYS; Post_Pin_1.0
R2: 14.0k; R_0402_1005Metric
R3: 22.6k; R_0402_1005Metric
R4: 102k; R_0402_1005Metric
R5: 30.1k; R_0402_1005Metric
R6, R18: 10.0k; R_0402_1005Metric
R7: 1.00k; R_0402_1005Metric
R13: 95.3k 0.5%; R_0402_1005Metric
R14, R16: 10.0k 0.5%; R_0402_1005Metric
R15: 93.1k 0.5%; R_0402_1005Metric
R17: 30.9k; R_0402_1005Metric
R43, R45, R47: 10R; R_0402_1005Metric
R44, R46, R48: 33R 0.5W; R_0805_2012Metric
R49, R51, R53, R58, R59: 100k; R_0402_1005Metric
R50, R52, R54: 470k; R_0402_1005Metric
R55, R56: 4.7k; R_0402_1005Metric
R57, R60: 10k; R_0402_1005Metric
U1: HUSB238_002DD; DFN-10-1EP_3x3mm_P0.5mm_EP1.65x2.38mm; MPN HUSB238_002DD; LCSC C7471904
U2: TPS259470ARPWR; TI_RPW0010A_VQFN-HR-10_2x2_PLACEHOLDER; MPN TPS259470ARPWR; LCSC C3662799
U4: TPS7A4901DGNR; HVSSOP-8-1EP_3x3mm_P0.65mm_EP1.57x1.89mm; MPN TPS7A4901DGNR; LCSC C16430
U5: TPS7A3001DGNR; HVSSOP-8-1EP_3x3mm_P0.65mm_EP1.57x1.89mm; MPN TPS7A3001DGNR; LCSC C33835
U6: TPS62933FDRLR; SOT-583-8; MPN TPS62933FDRLR; LCSC C5219272
U10: SN74LVC3G07DCUR; VSSOP-8_2.3x2mm_P0.5mm; MPN SN74LVC3G07DCUR; LCSC C131955
U11, U12, U13: TMUX7212RUMR; QFN-16-1EP_4x4mm_P0.65mm_EP2.5x2.5mm; MPN TMUX7212RUMR; LCSC C3657300
U14: TCA9535RGER; Texas_RGE0024C_VQFN-24-1EP_4x4mm_P0.5mm_EP2.1x2.1mm; MPN TCA9535RGER; LCSC C527428

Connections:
3V3: C32.1, C33.1, C53.1, C60.1, D5.2, D6.2, D7.2, H3.8, L2.2, R17.1, R44.1, R46.1, R48.1, R50.2, R52.2, R54.2, R55.2, R56.2, R57.2, R60.2, U10.8, U14.21 (VCC)
BOOST: C22.1, H3.5, U4.8 (IN)
BOOST_EN: H3.7, U14.17
BST_3: C28.1, U6.6 (BST)
CC1: D1.1, H1.7, U1.4 (CC1)
CC2: D2.1, H2.8, U1.5 (CC2)
CV1_S: H3.11, U11.1 (S1)
CV2_S: H3.12, U12.1 (S1)
CV3_S: H4.11, U13.1 (S1)
DN: H2.11, H4.4
DP: H2.9, H4.6
EFUSE_FLT: R60.1, U2.4 (FLT), U14.12
EF_DVDT: C7.1, U2.7 (dVdt)
EF_EN: R4.2, R5.1, U2.1 (EN/UVLO)
EF_ILM: R7.1, U2.9 (ILM)
EF_OV: R5.2, R6.1, U2.2 (OVLO)
EF_TMR: C8.1, U2.10 (ITIMER)
FB_3: R17.2, R18.1, U6.8 (FB)
GND: C6.2, C7.2, C8.2, C9.2, C10.2, C21.2, C22.2, C23.2, C24.2, C26.2, C27.2, C29.2, C30.2, C31.2, C32.2, C33.2, C53.2, C54.2, C55.2, C56.2, C57.2, C58.2, C59.2, C60.2, D1.2, D2.2, D5.1, D6.1, D7.1, H1.4, H1.8, H1.10, H1.12, H2.3, H2.7, H4.2, MP1.1, R2.2, R3.2, R6.2, R7.2, R14.2, R16.2, R18.2, R58.2, R59.2, U1.11 (GND), U2.8 (GND), U4.4 (GND), U4.9 (PAD), U5.4 (GND), U5.9 (PAD), U6.1 (RT), U6.4 (GND), U10.4, U11.3 (GND), U11.4 (S4), U11.5 (D4), U11.6 (SEL4), U11.10 (NC), U11.17 (PAD), U12.3 (GND), U12.4 (S4), U12.5 (D4), U12.6 (SEL4), U12.10 (NC), U12.17 (PAD), U13.3 (GND), U13.4 (S4), U13.5 (D4), U13.6 (SEL4), U13.10 (NC), U13.17 (PAD), U14.9 (GND), U14.18 (A0), U14.23 (A1), U14.24 (A2), U14.25 (PAD)
IO_INT: H4.5, R57.1, U14.22 (INT)
ISET: R3.1, U1.9 (ISET)
J1_RING: H1.6, R49.1, U11.8 (D3)
J1_TIP: H1.2, H3.9, U11.13 (D2), U11.16 (D1)
J2_RING: H1.5, R51.1, U12.8 (D3)
J2_TIP: H1.1, H3.10, U12.13 (D2), U12.16 (D1)
J3_RING: H2.6, R53.1, U13.8 (D3)
J3_TIP: H2.2, H4.9, U13.13 (D2), U13.16 (D1)
J4_RING: H2.5, H4.10
J4_TIP: H2.1, H4.12
MIDI_TX: H4.7, U10.1, U10.3, U10.6
MR1: R44.2, U11.9 (S3)
MR2: R46.2, U12.9 (S3)
MR3: R48.2, U13.9 (S3)
MT1: R43.2, U11.12 (S2)
MT2: R45.2, U12.12 (S2)
MT3: R47.2, U13.12 (S2)
MY1: R43.1, U10.7
MY2: R45.1, U10.5
MY3: R47.1, U10.2
N12V: C25.1, C27.1, C55.1, C57.1, C59.1, H3.4, R15.1, U5.1 (OUT), U11.2 (VSS), U12.2 (VSS), U13.2 (VSS)
N12_EN: R59.1, U5.5 (EN), U14.14
N_FB: C25.2, R15.2, R16.1, U5.2 (FB)
N_NR: C26.1, U5.6 (NR/SS)
P12V5: C20.1, C23.1, C54.1, C56.1, C58.1, H3.6, R13.1, U4.1 (OUT), U11.11 (VDD), U12.11 (VDD), U13.11 (VDD)
P12_EN: R58.1, U4.5 (EN), U14.7 (P06)
P_FB: C20.2, R13.2, R14.1, U4.2 (FB)
P_NR: C21.1, U4.6 (NR/SS)
QGND: H1.3, H2.4, H3.2, H4.8
RS1: D5.3, R49.2, R50.1, U14.1 (P00)
RS2: D6.3, R51.2, R52.1, U14.16
RS3: D7.3, R53.2, R54.1, U14.13
SCL: H4.3, R55.1, U1.7 (SCL), U14.19 (SCL)
SDA: H4.1, R56.1, U1.6 (SDA), U14.20 (SDA)
SS_3: C29.1, U6.7 (SS)
SW1_CV: U11.15 (SEL1), U14.11
SW1_MR: U11.7 (SEL3), U14.8 (P07)
SW1_MT: U11.14 (SEL2), U14.10
SW2_CV: U12.15 (SEL1), U14.3 (P02)
SW2_MR: U12.7 (SEL3), U14.6 (P05)
SW2_MT: U12.14 (SEL2), U14.4 (P03)
SW3_CV: U13.15 (SEL1), U14.2 (P01)
SW3_MR: U13.7 (SEL3), U14.15
SW3_MT: U13.14 (SEL2), U14.5 (P04)
SW_3: C28.2, L2.1, U6.5 (SW)
VBUS: C6.1, C9.1, H1.9, H1.11, H2.10, H2.12, R4.1, U1.1 (VIN), U2.5 (IN)
VNEG_RAW: C24.1, H3.3, U5.8 (IN)
VSET: R2.1, U1.8 (VSET)
VSYS: C10.1, C30.1, C31.1, H3.1, MP2.1, U2.6 (OUT), U6.3 (VIN)

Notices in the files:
tools/main_board_pinmap.py:
Reads ST's open pin data (github.com/STMicroelectronics/STM32_open_pin_data, BSD-3-Clause, (c) 2020 STMicroelectronics; not copied
